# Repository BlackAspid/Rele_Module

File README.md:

# Rele Module

_This is a rele module for electronic projects. It´s can used with &copy;Arduino, &copy;Microchip PIC.... Design in [KIcad](https://www.kicad.org/)._

## Starting 🚀

_You can clone this repo with this command, first go to the desired folder in your terminal._

```git clone https://github.com/BlackAspid/Rele_Module.git```

### Pre-requirements 📋

* Install [Kicad](https://www.kicad.org/download/) Vanilla from this link.

### Bill of Materials (BOM)

Quantity|Name|Digikey Code|Kicad Library
--------------|--------------|--|--
02|Screw Terminal 01x03|[ED10562-ND](https://www.digikey.com.mx/product-detail/es/on-shore-technology-inc/OSTVN03A150/ED10562-ND/1588863)|Connector
01|LED|[C503B-ACN-CY0Z0252-030CT-ND](https://www.digikey.com.mx/product-detail/es/cree-inc/C503B-ACN-CY0Z0252-030/C503B-ACN-CY0Z0252-030CT-ND/6138527)|Device
03|Resistor|[CF14JT1K00CT-ND](https://www.digikey.com.mx/product-detail/es/stackpole-electronics-inc/CF14JT1K00/CF14JT1K00CT-ND/1830350)|Device
01|1N4001|[641-1310-1-ND](https://www.digikey.com.mx/product-detail/es/comchip-technology/1N4001-G/641-1310-1-ND/1979675)|Diode
01|Sanyou SRD Form C|[PB2032-ND](https://www.digikey.com.mx/product-detail/es/te-connectivity-potter-brumfield-relays/ORWH-SH-105D1F-000/PB2032-ND/4925028)|Relay
01|2N3904|[2N3904FS-ND](https://www.digikey.com.mx/product-detail/es/on-semiconductor/2N3904BU/2N3904FS-ND/1413)|Transistor BJT

### Setting up 🔧
_Clone this repository_

```
git clone https://github.com/BlackAspid/Rele_Module.git
```

_Open Kicad program_

_Press File -> Open project (Ctrl + O)_

_Select file .pro_

_Here we go that's all, you can add or remove things_

## Ejecutando las pruebas ⚙️

_Explica como ejecutar las pruebas automatizadas para este sistema_

### Analice las pruebas end-to-end 🔩

_Explica que verifican estas pruebas y por qué_

```
Da un ejemplo
```

### Y las pruebas de estilo de codificación ⌨️

_Explica que verifican estas pruebas y por qué_

```
Da un ejemplo
```

## Despliegue 📦

_Agrega notas adicionales sobre como hacer deploy_

## Construido con 🛠️

_Menciona las herramientas que utilizaste para crear tu proyecto_

* [Dropwizard](http://www.dropwizard.io/1.0.2/docs/) - El framework web usado
* [Maven](https://maven.apache.org/) - Manejador de dependencias
* [ROME](https://rometools.github.io/rome/) - Usado para generar RSS

## Contribuyendo 🖇️

Por favor lee el [CONTRIBUTING.md](https://gist.github.com/villanuevand/xxxxxx) para detalles de nuestro código de conducta, y el proceso para enviarnos pull requests.

## Wiki 📖

Puedes encontrar mucho más de cómo utilizar este proyecto en nuestra [Wiki](https://github.com/tu/proyecto/wiki)

## Versionado 📌

Usamos [SemVer](http://semver.org/) para el versionado. Para todas las versiones disponibles, mira los [tags en este repositorio](https://github.com/tu/proyecto/tags).

## Licencia 📄

Este proyecto está bajo la Licencia (Tu Licencia) - mira el archivo [LICENSE.md](LICENSE.md) para detalles

## Expresiones de Gratitud 🎁<!--  -->

* Comenta a otros sobre este proyecto 📢
* Invita una cerveza 🍺 o un café ☕ a alguien del equipo. 
* Da las gracias públicamente 🤓.
* etc.

## Autors ✒️
* **Black Aspid** - *Trabajo Inicial*, *Documentación* - [blackaspid](https://github.com/BlackAspid)

También puedes mirar la lista de todos los [contribuyentes](https://github.com/your/project/contributors) quíenes han participado en este proyecto.  -->
---
⌨️ con ❤️ por [Villanuevand](https://github.com/Villanuevand) 😊

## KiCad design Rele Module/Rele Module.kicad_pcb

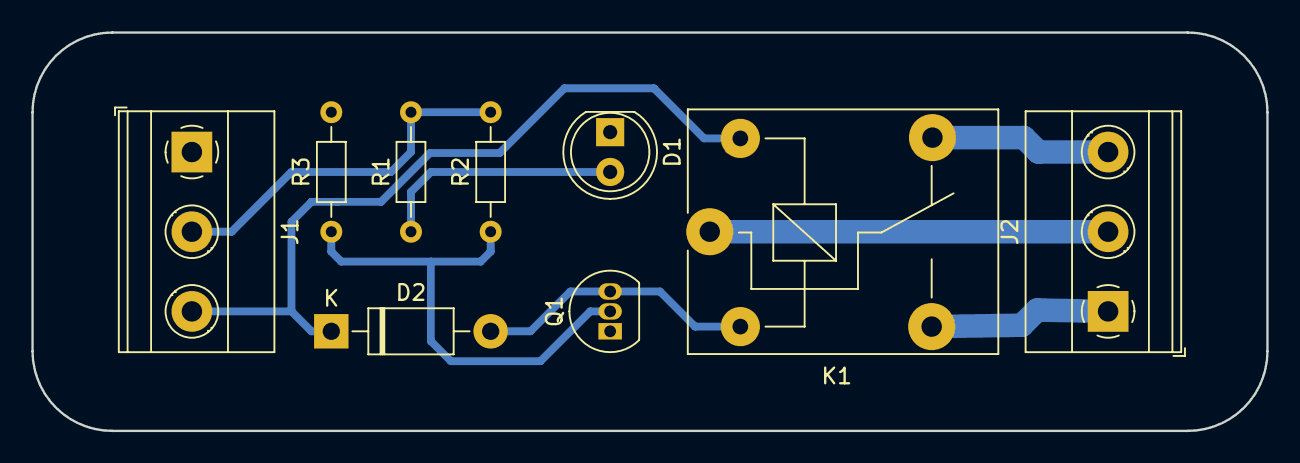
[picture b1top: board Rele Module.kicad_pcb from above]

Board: 2 copper layers, 78.7 x 25.4 mm, 9 parts (0 on the bottom side), 9 nets.

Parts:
D1: LED; LED_D5.0mm
D2: 1N4002; D_DO-41_SOD81_P10.16mm_Horizontal
J1, J2: Screw_Terminal_01x03; TerminalBlock_Phoenix_MKDS-1,5-3-5.08_1x03_P5.08mm_Horizont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
K1: SANYOU_SRD_Form_C; Relay_SPDT_SANYOU_SRD_Series_Form_C
Q1: 2N3904; TO-92_Inline
R1, R2, R3: R; R_Axial_DIN0204_L3.6mm_D1.6mm_P7.62mm_Horizontal

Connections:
GND: D1.1, J1.1, Q1.1, R3.2
unnamed: D1.2, R1.2
unnamed: D2.2, K1.2, Q1.3
unnamed: J1.2, R1.1, R2.2
unnamed: J2.1, K1.3
unnamed: J2.2, K1.1
unnamed: J2.3, K1.4
unnamed: Q1.2, R2.1, R3.1
VCC: D2.1, J1.3, K1.5

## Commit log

2020-11-17 Create initial files for the project
2020-11-17 Complete Esquematic
2020-11-17 Annotation Complete
2020-11-17 partially mapped footprints
2020-11-30 Main Commit
2020-11-30 Make pcb connections
2020-12-07 pcb track widening
2020-12-07 Project completed
2020-12-08 Added Images
2020-12-08 Added Readme.md
2021-01-15 Added Autors
2021-01-18 Added Setting up
